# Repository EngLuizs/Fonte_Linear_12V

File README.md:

# FONTE LINEAR AJUSTÁVEL 12V 1A COM MONITORAMENTO

Projeto desenvolvido pela equipe **FLM System** utilizando ESP32, KiCad e PlatformIO para controle, monitoramento e interface web de uma fonte linear regulada ajustável.

---

# Descrição do Projeto

O projeto consiste em uma fonte linear ajustável de até 12V e 1A com:

- Monitoramento de tensão, corrente e potência
- Interface Web via ESP32
- Display LCD I2C 20x4
- Medição analógica calibrada
- Indicação visual por LED
- PCB dedicada desenvolvida no KiCad
- Controle e aquisição utilizando ESP32-WROOM-32E

O sistema disponibiliza os dados em tempo real tanto no display LCD quanto em uma página web hospedada diretamente pelo ESP32 em modo Access Point.

---

# Funcionalidades

- Leitura de tensão de saída
- Leitura de corrente utilizando resistor shunt
- Cálculo automático de potência
- Web Server integrado
- Interface Web responsiva
- Calibração de tensão e corrente
- LEDs indicadores de status
- Comunicação I2C com display LCD
- Sistema de proteção visual por sobrecorrente

---

# Hardware Utilizado

## Processador
- ESP32-WROOM-32E

## Reguladores
- LM7812
- LM2576
- LD1117

## Componentes principais
- LM358
- TIP120
- BC547
- LCD I2C 20x4
- Shunt 0.22Ω / 5W 
- Shunt 0,33Ω / 5W

---

# Estrutura do Projeto

```text
Firmware/       -> Código fonte do ESP32
Hardware/            -> Esquemáticos, PCB e Gerbers
Documentação/   -> Relatórios e documentação
Estrutura/      -> Estruturas e peças mecânicas
```

---

# Firmware

O firmware foi desenvolvido utilizando:

- Visual Studio Code
- PlatformIO
- Framework Arduino para ESP32

## Principais bibliotecas

- Arduino.h
- Wire.h
- LiquidCrystal_I2C
- WiFi.h
- WebServer.h

---

# Interface Web

O ESP32 opera em modo Access Point criando a rede:

```text
SSID: FLM_FTE12V
Senha: 11110000
```

Após conexão, o sistema disponibiliza:
- Página web embarcada
- Dados em JSON
- Monitoramento em tempo real

---

# Monitoramento

O sistema realiza:

- Média de amostras ADC
- Filtragem sincronizada em 60Hz
- Correção de offset
- Calibração linear de tensão e corrente

---

# PCB e Projeto Eletrônico

O projeto eletrônico foi desenvolvido no:

- KiCad

Incluindo:
- Esquemático completo
- PCB dedicada
- Gerbers de fabricação
- Instrumentação analógica
- Fonte linear regulada
- Conversores DC-DC auxiliares

---

# Organização de Versionamento

Este projeto utiliza:

- Git
- GitHub

Para:
- Controle de revisões
- Histórico de alterações
- Backup
- Versionamento de firmware e PCB

---

# Equipe

FLM System

---

# Versão Atual

```text
Versão Firmware: 0.02.01
Última Revisão: 01/05/2026
```

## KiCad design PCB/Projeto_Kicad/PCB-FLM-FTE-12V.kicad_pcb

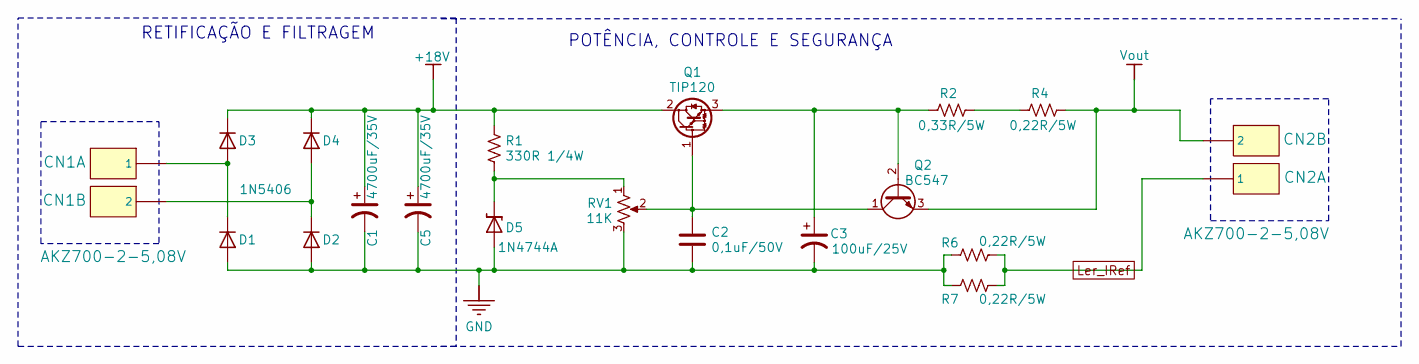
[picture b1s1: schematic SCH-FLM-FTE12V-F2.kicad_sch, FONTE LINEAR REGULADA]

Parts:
C1, C5: 4700uF/35V; CP_Radial_D18.0mm_P7.50mm
C2: 0,1uF/50V; C_Disc_D5.0mm_W2.5mm_P5.00mm
C3: 100uF/25V; CAP100UF25V
CN1, CN2: AKZ700-2-5,08V; AKZ300-2-5.08
D1, D2, D3, D4: 1N5406; D_DO-201AD_P15.24mm_Horizontal
D5: 1N4744A; D_DO-41_SOD81_P10.16mm_Horizontal
Q1: TIP120; TO-220-3_Vertical
Q2: BC547; TRANSP(CBE)_BC547
R1: 330R 1/4W; R_Axial_DIN0207_L6.3mm_D2.5mm_P7.62mm_Horizontal
R2: 0,33R/5W; R_Axial_DIN0516_L15.5mm_D5.0mm_P5.08mm_Vertical
R4, R6, R7: 0,22R/5W; R_Axial_DIN0516_L15.5mm_D5.0mm_P5.08mm_Vertical
RV1: 11K; POTENCIOMETRO

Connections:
+18V: C1.1, C5.1, D3.1 (K), D4.1 (K), Q1.2 (C), R1.1; also elsewhere on the board
GND: C1.2, C2.2, C3.2, C5.2, D1.2 (A), D2.2 (A), D5.2 (A), R6.2, R7.2, RV1.3; also elsewhere on the board
Ler_IRef: CN2.1, R6.1, R7.1; also elsewhere on the board
unnamed: CN1.1, D1.1 (K), D3.2 (A)
unnamed: CN1.2, D2.1 (K), D4.2 (A)
unnamed: D5.1 (K), R1.2, RV1.1
unnamed: C2.1, Q1.1 (B), Q2.1 (C), RV1.2
unnamed: C3.1, Q1.3 (E), Q2.2 (B), R2.1
unnamed: R2.2, R4.1
Vout: CN2.2, Q2.3 (E), R4.2; also elsewhere on the board

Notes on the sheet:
RETIFICAÇÃO E FILTRAGEM
POTÊNCIA, CONTROLE E SEGURANÇA

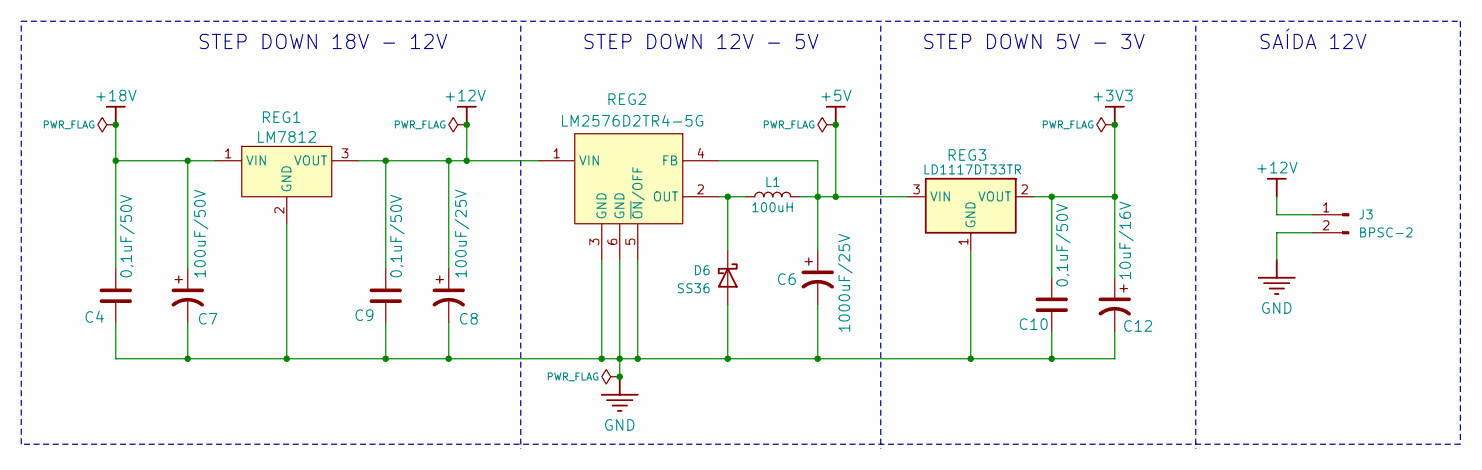
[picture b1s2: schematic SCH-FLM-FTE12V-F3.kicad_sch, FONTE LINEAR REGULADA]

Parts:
C4, C9, C10: 0,1uF/50V; C_Disc_D5.0mm_W2.5mm_P5.00mm
C6: 1000uF/25V; CAP_1000UF_50V
C7: 100uF/50V; CAP100UF25V
C8: 100uF/25V; CAP100UF25V
C12: 10uF/16V; CAP100UF25V
D6: SS36; DO-214AA_SMB_J-BEND
J3: BPSC-2; PinSocket_1x02_P2.54mm_Vertical
L1: 100uH; 74477120
REG1: LM7812; LM78XX
REG2: LM2576D2TR4-5G; D2PAK-5
REG3: LD1117DT33TR; DPAK_LD1117; Mouser Part Number 511-LD1117DT33-TR

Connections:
+3V3: C10.1, C12.1, REG3.2 (VOUT); also elsewhere on the board
+5V: C6.1, L1.2, REG2.4 (FB), REG3.3 (VIN); also elsewhere on the board
+12V: C8.1, C9.1, J3.1, REG1.3 (VOUT), REG2.1 (VIN); also elsewhere on the board
+18V: C4.1, C7.1, REG1.1 (VIN); also elsewhere on the board
GND: C4.2, C6.2, C7.2, C8.2, C9.2, C10.2, C12.2, D6.2 (A), J3.2, REG1.2 (GND), REG2.3 (GND), REG2.5 (~ON/OFF), REG2.6 (GND), REG3.1 (GND); also elsewhere on the board
unnamed: D6.1 (K), L1.1, REG2.2 (OUT)

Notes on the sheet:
SAÍDA 12V
STEP DOWN 18V - 12V
STEP DOWN 12V - 5V
STEP DOWN 5V - 3V

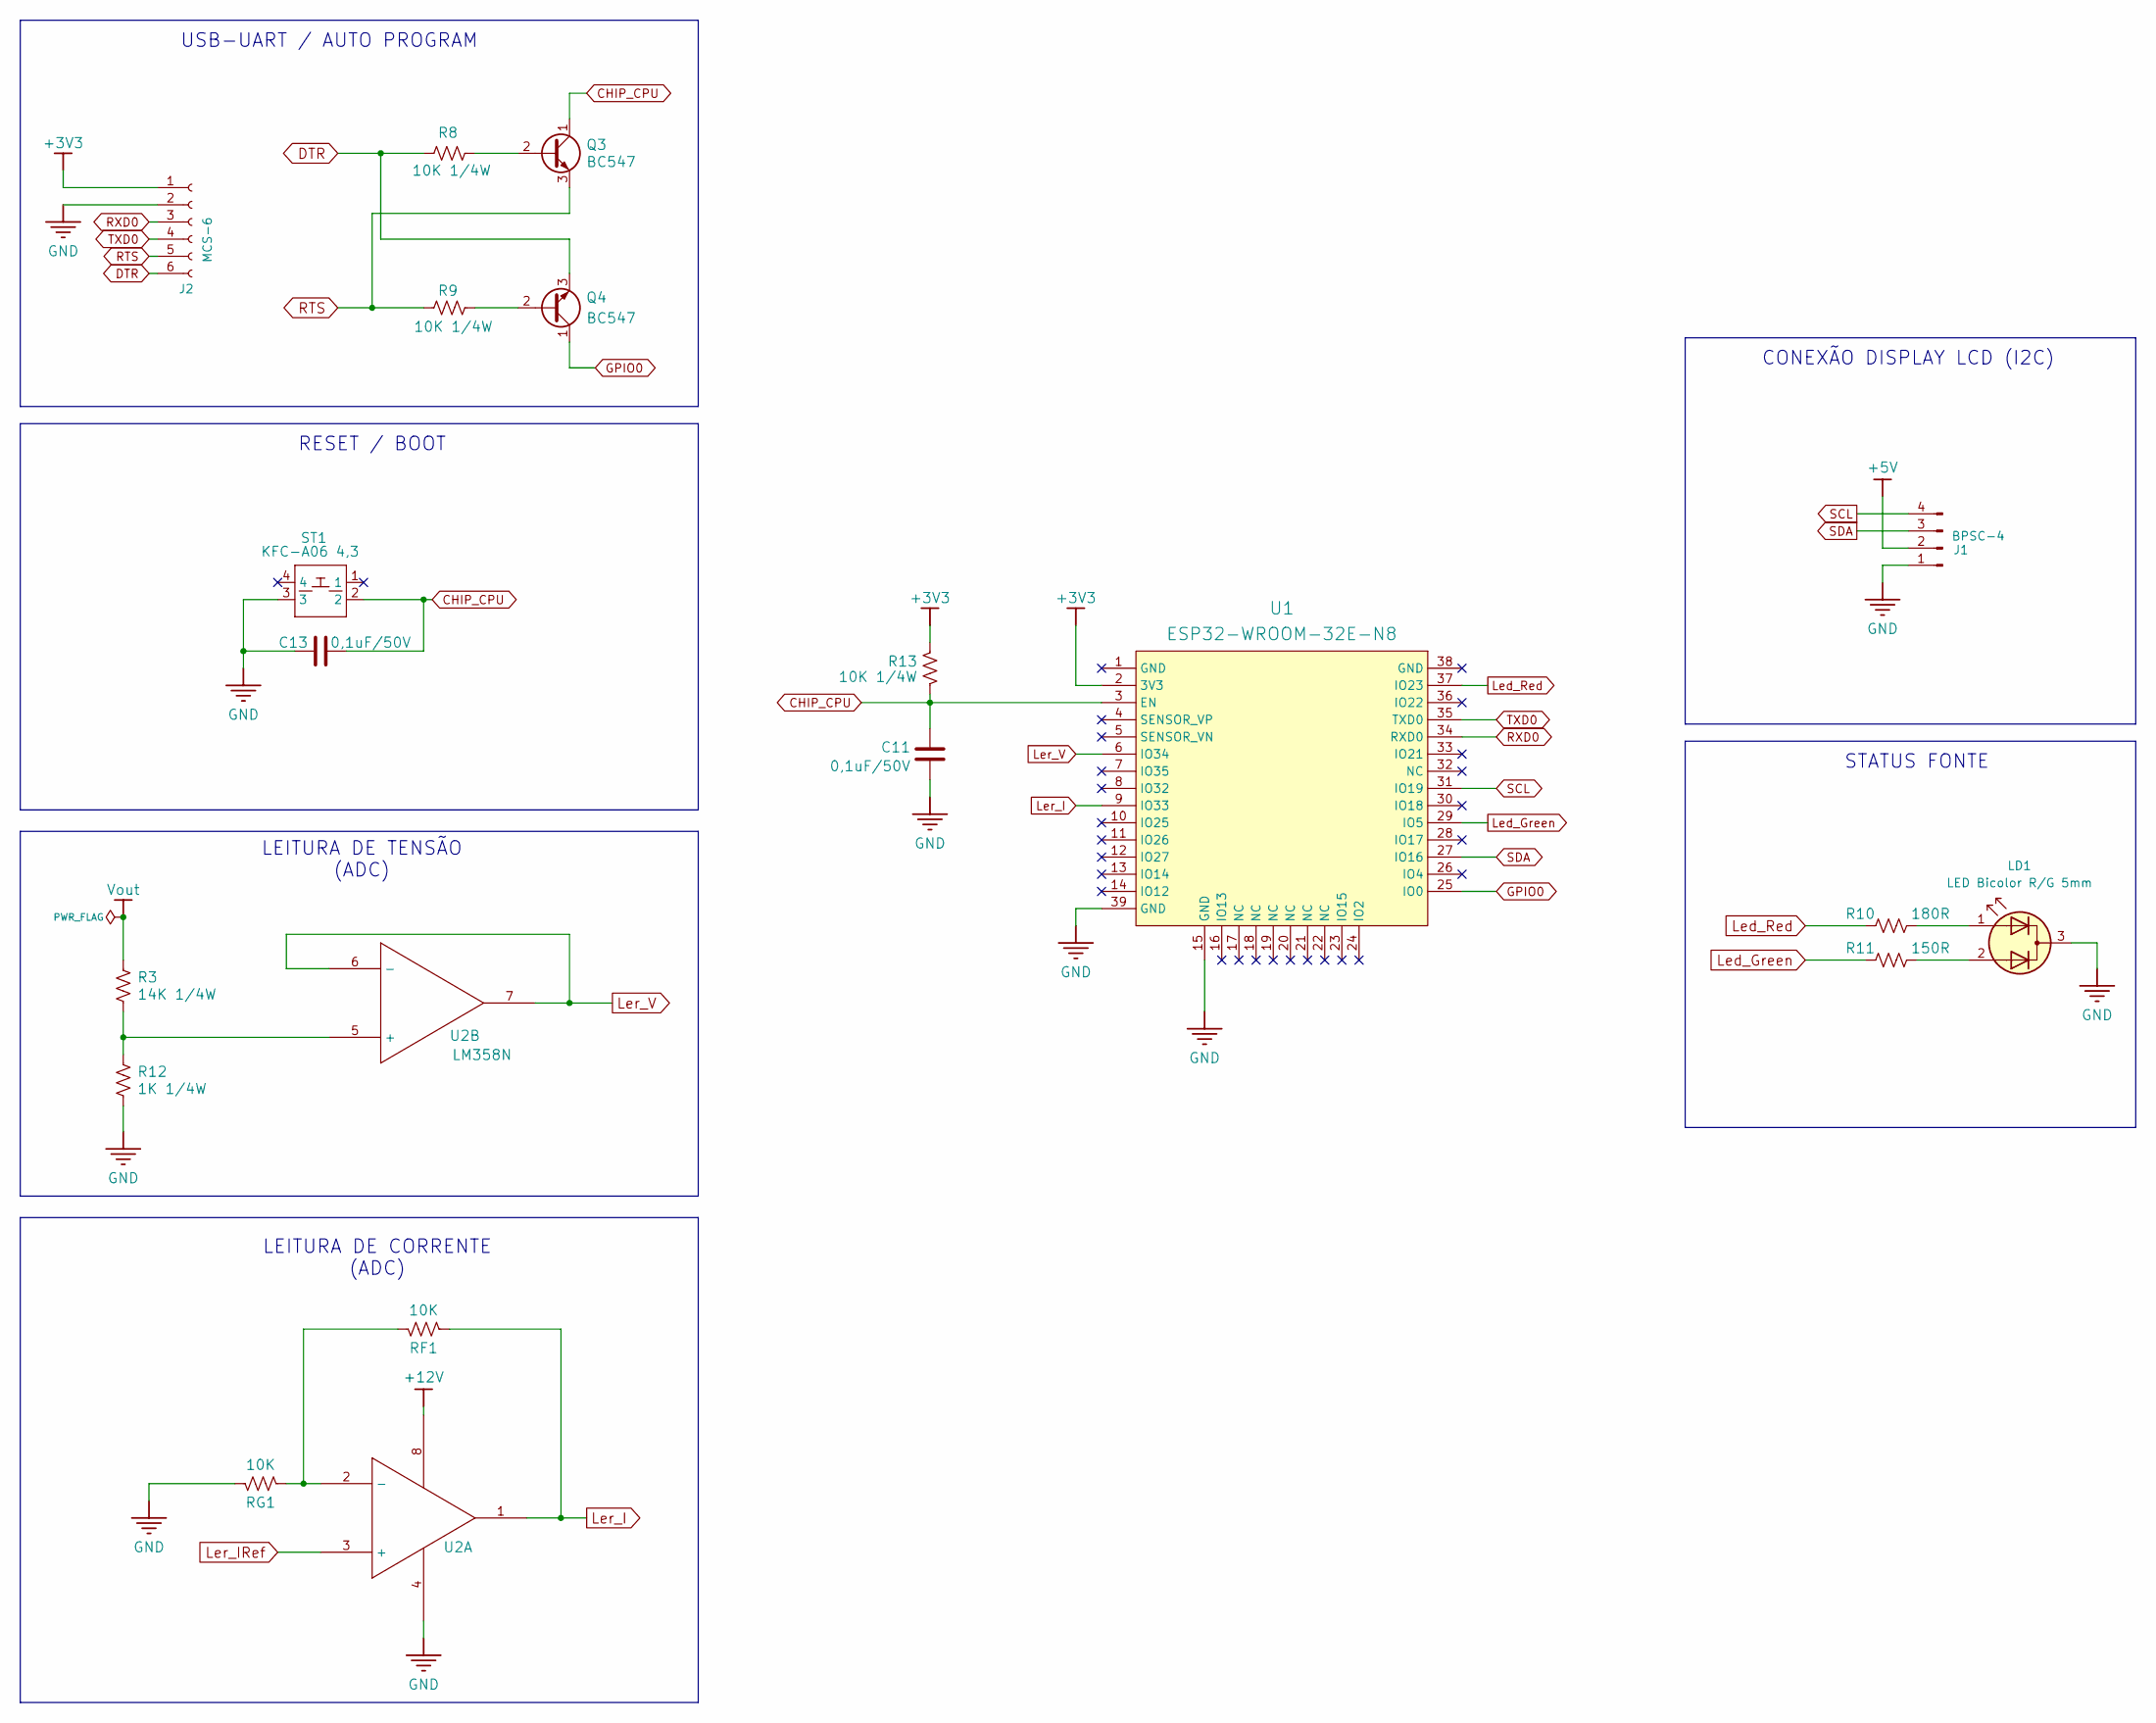
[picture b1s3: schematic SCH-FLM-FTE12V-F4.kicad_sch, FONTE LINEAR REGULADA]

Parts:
C11, C13: 0,1uF/50V; C_Disc_D5.0mm_W2.5mm_P5.00mm
J1: BPSC-4; PinHeader_1x04_P2.54mm_Vertical
J2: MCS-6; PinSocket_1x06_P2.54mm_Vertical
LD1: LED Bicolor R/G 5mm; LED5MM_BICOLOR_K
Q3, Q4: BC547; TRANSP(CBE)_BC547
R3: 14K 1/4W; R_Axial_DIN0207_L6.3mm_D2.5mm_P7.62mm_Horizontal
R8, R9, R13: 10K 1/4W; R_Axial_DIN0207_L6.3mm_D2.5mm_P7.62mm_Horizontal
R10: 180R; R_Axial_DIN0207_L6.3mm_D2.5mm_P7.62mm_Horizontal
R11: 150R; R_Axial_DIN0207_L6.3mm_D2.5mm_P7.62mm_Horizontal
R12: 1K 1/4W; R_Axial_DIN0207_L6.3mm_D2.5mm_P7.62mm_Horizontal
RF1: 10K; R_Axial_DIN0207_L6.3mm_D2.5mm_P2.54mm_Vertical
RG1: 10K; R_Axial_DIN0207_L6.3mm_D2.5mm_P2.54mm_Vertical
ST1: KFC-A06 4,3; PUSHBOTON
U1: ESP32-WROOM-32E-N8
U2: LM358N; DIP8

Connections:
+3V3: J2.1, R13.2, U1.2 (3V3); also elsewhere on the board
+5V: J1.2; also elsewhere on the board
+12V: U2.8 (V+); also elsewhere on the board
CHIP_CPU: C11.1, C13.2, Q3.1 (C), R13.1, ST1.2, U1.3 (EN)
DTR: J2.6, Q4.3 (E), R8.1
GND: C11.2, C13.1, J1.1, J2.2, LD1.3 (K), R12.2, RG1.1, ST1.3, U1.15 (GND), U1.39 (GND), U2.4 (GND); also elsewhere on the board
GPIO0: Q4.1 (C), U1.25 (IO0)
Led_Green: R11.1, U1.29 (IO5)
Led_Red: R10.1, U1.37 (IO23)
Ler_I: RF1.2, U1.9 (IO33), U2.1 (OUT)
Ler_IRef: U2.3 (+); also elsewhere on the board
Ler_V: U1.6 (IO34), U2.6 (-), U2.7 (OUT)
unnamed: LD1.1 (A1), R10.2
unnamed: LD1.2 (A2), R11.2
unnamed: Q3.2 (B), R8.2
unnamed: Q4.2 (B), R9.2
unnamed: RF1.1, RG1.2, U2.2 (-)
unnamed: R3.2, R12.1, U2.5 (+)
RTS: J2.5, Q3.3 (E), R9.1
RXD0: J2.3, U1.34 (RXD0)
SCL: J1.4, U1.31 (IO19)
SDA: J1.3, U1.27 (IO16)
TXD0: J2.4, U1.35 (TXD0)
Vout: R3.1; also elsewhere on the board

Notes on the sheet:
STATUS FONTE
RESET / BOOT
USB-UART / AUTO PROGRAM
LEITURA DE CORRENTE (ADC)
LEITURA DE TENSÃO (ADC)
CONEXÃO DISPLAY LCD (I2C)

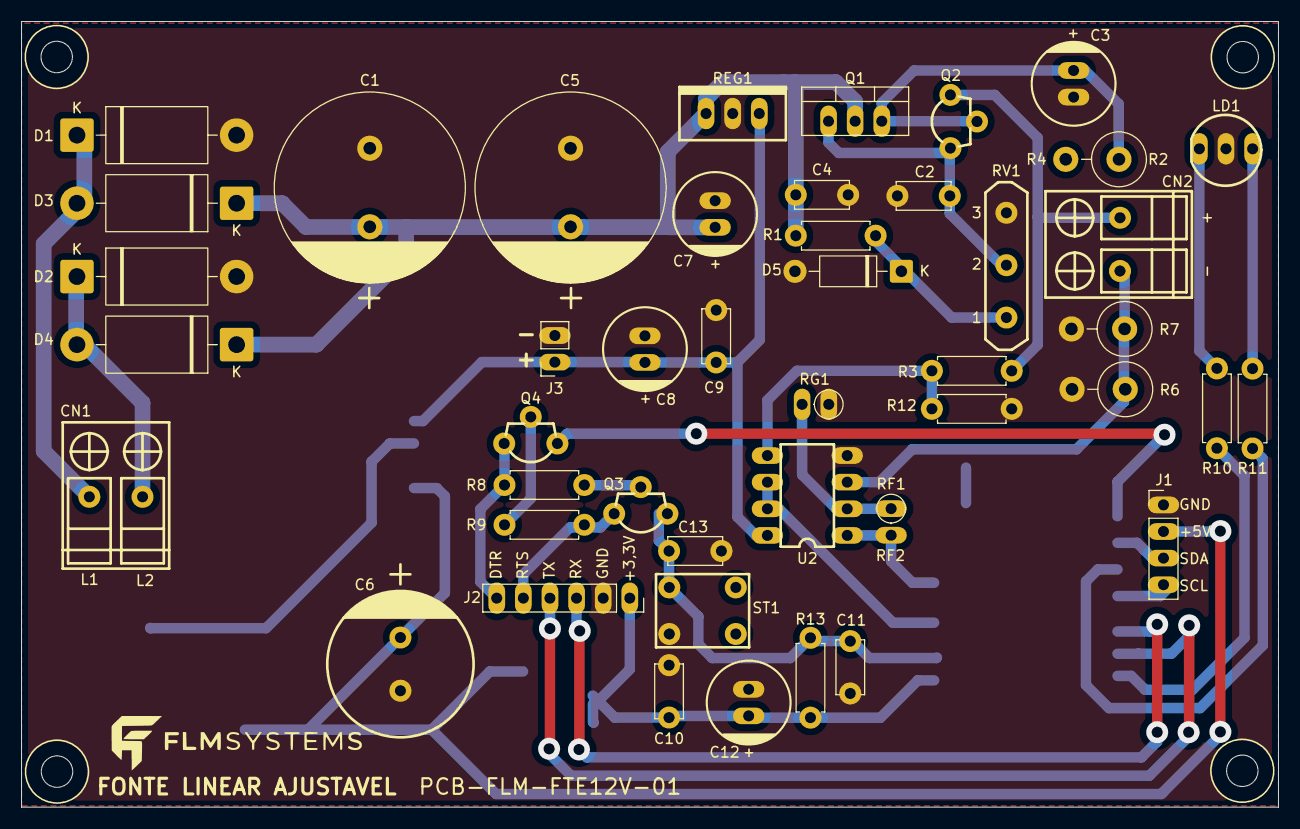
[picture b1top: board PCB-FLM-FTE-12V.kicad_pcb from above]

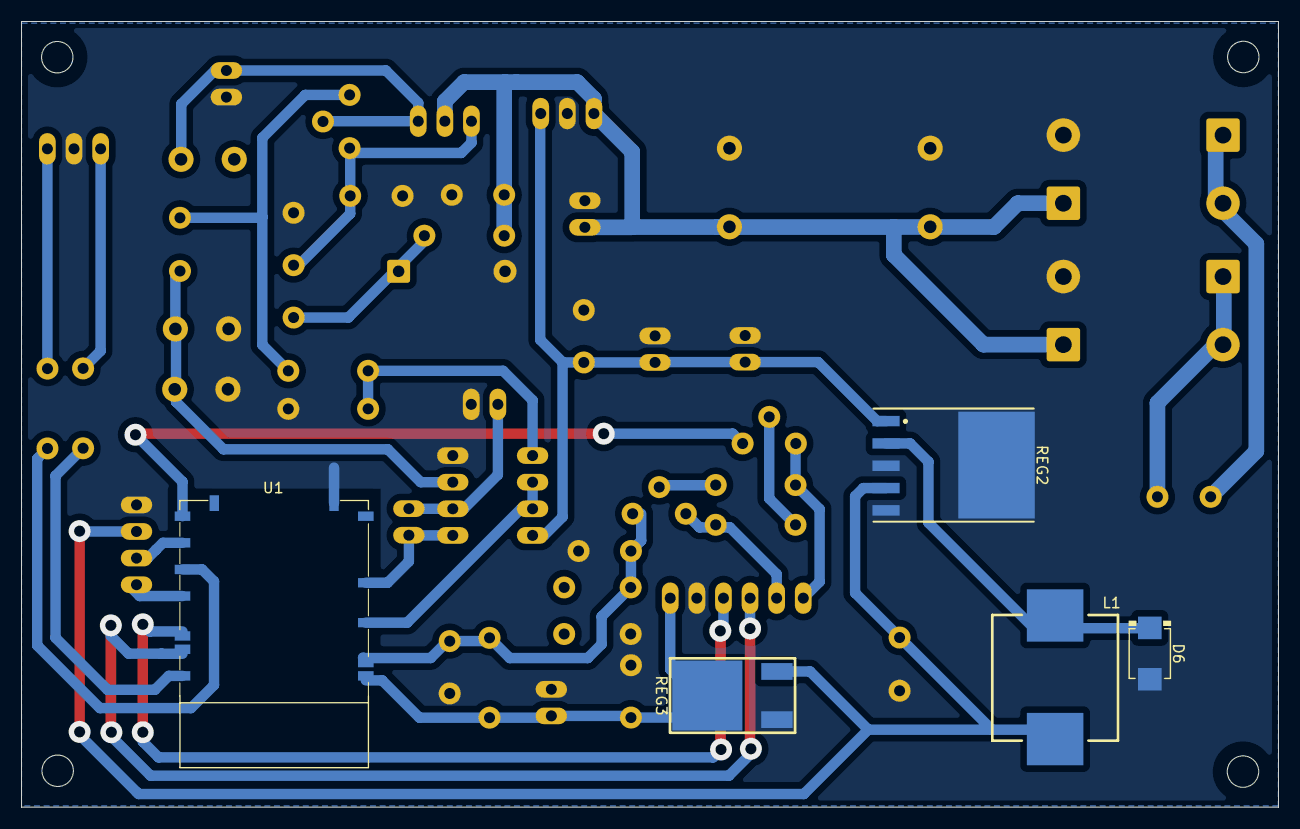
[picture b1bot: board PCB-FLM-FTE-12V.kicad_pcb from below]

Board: 2 copper layers, 120.0 x 75.0 mm, 54 parts (5 on the bottom side), 31 nets.

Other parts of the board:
Furo11, Furo11#2, Furo11#3, Furo11#4: Furo 3mm

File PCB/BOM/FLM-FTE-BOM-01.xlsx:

PROJETO: Fonte Linear Regulada 12V
Cód. Sisgem: | Referencia | Valor | Quantidade | Footprint
 | CN1,CN2 | AKZ700-2-5,08V | 2 | PCB-CONECTOR:AKZ300-2-5.08
 | Q1 | TIP120 | 1 | Package_TO_SOT_THT:TO-220-3_Vertical
 | R2,R6 | 0,22R/5W | 3 | Resistor_THT:R_Axial_DIN0516_L15.5mm_D5.0mm_P5.08mm_Vertical
 | RV1 | 10K | 1 | PCB-DISCRETO:POTENCIOMETRO
010136 | R5,R12 | 1K 1/4W | 2 | Resistor_THT:R_Axial_DIN0207_L6.3mm_D2.5mm_P7.62mm_Horizontal
010183 | Q2,Q3,Q4 | BC547 | 3 | PCB-DISCRETO:TRANSP(CBE)_BC547
010286 | REG1 | LM7812 | 1 | PCB-CI:TO-220
112805 | J1 | BPSC-4 | 1 | Connector_PinHeader_2.54mm:PinHeader_1x04_P2.54mm_Vertical
113331 | C2,C4,C9,C10,C11,C13 | 0,1uF/50V | 6 | Capacitor_THT:C_Disc_D5.0mm_W2.5mm_P5.00mm
114334 | D5 | 1N4744A | 1 | Diode_THT:D_DO-41_SOD81_P10.16mm_Horizontal
114642 | ST1 | KFC-A06 4,3 | 1 | PCB-GERAL:PUSHBOTON
114715 | LD1 | LED Bicolor R/G 5mm | 1 | PCB-DISCRETO:LED5MM_BICOLOR_K
114841 | J2 | MCS-6 | 1 | Connector_PinSocket_2.54mm:PinSocket_1x06_P2.54mm_Vertical
119911 | D1,D2,D3,D4 | 1N5406 | 4 | Diode_THT:D_DO-201AD_P15.24mm_Horizontal
121835 | REG3 | LD1117DT33TR | 1 | PCB-CI:DPAK_LD1117
130379 | REG2 | LM2576D2TR4-5G | 1 | PCB-CI:D2PAK-5
130411 | D6 | SS36 | 1 | PCB-DISCRETO:DO-214AA_SMB_J-BEND
130483 | L1 | 100uH | 1 | PCB-GERAL:74477120
137742 | U1 | ESP32-WROOM-32E | 1 | PCB-GERAL:ESP32-WROOM-32E-N8
139388 | C3,C7,C8 | 100uF/25V | 3 | PCB-DISCRETO:CAP100UF25V
010121.133 | C12 | 10uF/16V | 1 | PCB-DISCRETO:CAP100UF25V
010121.290 | C6 | 1000uF/25V | 1 | PCB-DISCRETO:CAP_1000UF_50V
010121.338 | C1,C5 | 4700uF/25V | 2 | Capacitor_THT:CP_Radial_D16.0mm_P7.50mm
010132.208 | R11 | 150R | 1 | Resistor_THT:R_Axial_DIN0207_L6.3mm_D2.5mm_P7.62mm_Horizontal
010132.216 | R10 | 180R | 1 | Resistor_THT:R_Axial_DIN0207_L6.3mm_D2.5mm_P7.62mm_Horizontal
010132.240 | R1 | 330R 1/4W | 1 | Resistor_THT:R_Axial_DIN0207_L6.3mm_D2.5mm_P7.62mm_Horizontal
010136.576 | R3,R8,R9,R13 | 10K 1/4W | 4 | Resistor_THT:R_Axial_DIN0207_L6.3mm_D2.5mm_P7.62mm_Horizontal

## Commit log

2026-05-09 Substituição do C1 e C5
2026-05-10 Versão 02.00 - Atualização nos arquivos gerbers
2026-05-10 Alteração do arquivo README.md
2026-05-11 Reorganização de pastas e documentação
2026-05-11 Atualização do resistor shunt R2 e R4
2026-05-11 Atualização do arquivo 'FLM-FTE-SCH-01'
2026-05-12 Adição do R7 em paralelo com R6 e adição do RF2 de 15K e mudança de valor do RF1 de 10K para 15K
2026-05-12 Atualização dos arquivos para fabricação da PCB
    Foi alterado os arquivos gerber e também PDF do esquemático e PCB. Arquivos:
    'FLM-FTE-SCH-01'
    'FLM-FTE-PCB-FAB-01'
    'FLM-FTE-PCB-01'.
    Também foi feito a inclusão Datasheet ESP32
2026-05-13 Atualização arquivos Gerbers
2026-05-13 Inclusão dos arquivos G-Code
2026-05-13 Inclusão dos arquivos SVG para fabricação a laser
2026-05-14 Remoção dos Jumpers no TopSilkscreen
2026-05-14 Atualização da senha para acesso ao wifi do esp32 e README.md
2026-05-14 Alteração nos pinos de leitura de Tensão (PIN_V) e Corrente (PIN_I)
2026-05-14 Atualização do platformio.ini
2026-05-14 Alteração no 'ganho_I' para 4.0
2026-05-14 Atualização do PDF 'FLM-FTE-PCB-FAB-01'
2026-05-15 Alteração nos arquivos Drilling
2026-05-16 Atualização dos pinos LDRED e LDGREEN
2026-05-16 Alteração nos pinos do LED
2026-05-16 Alteração do valor resistor shunt para 0,55ohms
2026-05-16 Alteração resistor shunt
2026-05-16 Alteração no valor maximo e minimo de sobre corrente dos leds
2026-05-17 Inclusão do Relatorio Final da APS ao Github
2026-05-22 Atualização dos valores de calibração
2026-05-23 Resumo incluido
2026-05-23 Adicionado Calculos
2026-05-23 Atualização do esquemático - R7 opcional
2026-05-23 componentes anotados
2026-05-23 atualizacao
2026-05-23 Inclusão do arquivo FLM-FTE-PCB-3D-01
2026-05-24 Alteração no arquivo FLM-FTE-BOM-01
2026-05-25 Relatório Técnico - Fonte Linear Regulada
2026-05-25 Add MIT License to the project
2026-05-25 Inclusão do README.md do firmware
2026-05-25 Atualização dos dados de calibração
2026-05-28 Inclusção dos datasheet
2026-05-30 Inclusão dos arquivos de simulação
2026-05-31 Relatorio final V2
